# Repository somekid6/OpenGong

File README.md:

# OpenGong — Multilateration Electronic Target

> [!WARNING]
> **Work in progress.** OpenGong is incomplete and not yet fully built or tested. Designs, firmware and documentation may change, and parts of the system may not work as described. Build at your own risk.

Five piezo sensors bonded to the back of an AR500 steel plate locate bullet impacts to within about 5 mm by time-difference-of-arrival multilateration. An ESP32-S3 (Heltec WiFi LoRa 32 V3) timestamps each sensor in hardware, solves the impact position, and sends the coordinates over LoRa to a receiver at the firing line. The link is designed for 500 m, and about 1 km is a realistic planning figure on open ground. The estimated limit is 2–4 km on flat, open ground with clear line of sight. These are link-budget estimates, so run a [signal range test](docs/System-Design.md#96-signal-range-test) at your own site. It works with any single-projectile round the plate is rated for, from .22 LR to full-power rifle; shotgun pellets are not supported.

## Build guide

The [OpenGong wiki](https://github.com/somekid6/OpenGong/wiki) walks through the whole build in eleven steps. Start with [Step 1: Get the Project Files](https://github.com/somekid6/OpenGong/wiki/Step-1-Get-the-Project-Files).

1. [Get the Project Files](https://github.com/somekid6/OpenGong/wiki/Step-1-Get-the-Project-Files)
2. [Parts and Tools](https://github.com/somekid6/OpenGong/wiki/Step-2-Parts-and-Tools)
3. [Order the Analog Board](https://github.com/somekid6/OpenGong/wiki/Step-3-Order-the-Analog-Board)
4. [Print the Jig and Covers](https://github.com/somekid6/OpenGong/wiki/Step-4-Print-the-Jig-and-Covers)
5. [Assemble the Analog Board](https://github.com/somekid6/OpenGong/wiki/Step-5-Assemble-the-Analog-Board)
6. [Flash the Firmware](https://github.com/somekid6/OpenGong/wiki/Step-6-Flash-the-Firmware)
7. [Glue and Wire the Sensors](https://github.com/somekid6/OpenGong/wiki/Step-7-Glue-and-Wire-the-Sensors)
8. [Bench Bring-Up](https://github.com/somekid6/OpenGong/wiki/Step-8-Bench-Bring-Up)
9. [Calibrate](https://github.com/somekid6/OpenGong/wiki/Step-9-Calibrate)
10. [Enclosure and Mounting](https://github.com/somekid6/OpenGong/wiki/Step-10-Enclosure-and-Mounting)
11. [Range Setup and First Shots](https://github.com/somekid6/OpenGong/wiki/Step-11-Range-Setup-and-First-Shots)

If something doesn't work, see [Troubleshooting](https://github.com/somekid6/OpenGong/wiki/Troubleshooting) for symptoms and fixes covering bring-up, calibration and the radio link.

## Reference documents

The documents below hold the design reasoning, schematics and source files that the build guide draws on.

- [System design](docs/System-Design.md): architecture, accuracy budget, sensors, mounting and enclosure, solver, calibration, radio link and range, ammunition and safety, bill of materials and build plan.
- [Wiring diagram](docs/Wiring-Diagram.md): system wiring, per-channel circuit, shared bias/threshold/power, Heltec pin map and channel-to-part map.
- [Analog board PCB](hardware/analog-board/README.md): ready-to-order gerbers, BOM, assembly and bring-up for the 5-channel front end that the Heltec V3 plugs into, plus the KiCad project.
- [Placement jig](Placement%20Jig/README.md): the OpenSCAD sensor and punch-guide jig for rectangular and round plates, covering parameters, export, printing, assembly and calibration points.
- [Sensor covers](Sensor%20Cover/README.md): OpenSCAD cover pods and cable clips held on by rubber-coated pot magnets, with the magnet and hardware list, printing, fitting and removal for calibration.
- [Box brackets](Box%20Bracket/README.md): example OpenSCAD sketches of the bracket that hangs the electronics box from the plate's hanger bolts, for plates with one or two hanger holes. Square tube spacers and straight aluminium flat bar, with no bending, and a preview that checks clearance to the sensor pods. Custom fit to your plate.
- [Firmware](firmware/README.md): ESP32-S3 target (hardware capture, solver, on-board calibration, LoRa) and receiver firmware, with build, bring-up and calibration steps. The receiver hosts a [web app](firmware/README.md#web-app) over its own Wi-Fi that draws your plate to scale with the hits and an MOA/MIL grid on any phone or laptop.

The receiver's web app on a phone and a laptop: the plate to scale, numbered hits, an MOA or mil grid and the group statistics. It can also walk you through calibrating the target from your phone ([firmware README](firmware/README.md#web-app)).

<details>
<summary>Web app screenshots</summary>

</details>

## Safety

Follow your plate maker's rating for the round you shoot. [System design §10](docs/System-Design.md#10-ammunition-and-safety-read-before-shooting) lists commonly cited plate thicknesses and minimum distances per caliber. Never use steel-core or penetrator rounds. Keep all electronics and cables fully behind the plate under a steel shield.

## References and acknowledgements

OpenGong builds on the work of **Matthew Waterman and Donato Salazar**, whose Northern Illinois University senior design project showed that an accurate electronic target can be built from cheap, easy-to-find parts. Thank you both for publishing your research and source code so others could build on it.

- M. Waterman and D. Salazar, "Electronic Target," Senior Design II, Northern Illinois University (advisor: Dr. Abul Azad), December 8, 2011. [Paper (PDF)](docs/Reference%20Materials/Waterman%20Salazar%20-%20Electronic%20Targets.pdf) · [Presentation with notes (PDF)](docs/Reference%20Materials/Waterman%20Salazar%20Tech%20478%20Presentation%20With%20Notes.pdf). These were first published on etarg.net, which is no longer online, so copies are kept here.

Their paper sets out the core approach this project uses: timing the impact wave at piezo sensors on a hard target with threshold comparators, then locating the hit by time-difference-of-arrival multilateration. It also names the error sources this design sets out to remove. [System design §1](docs/System-Design.md#1-summary) compares the two.

AI assistance: [Claude](https://www.anthropic.com/claude), by Anthropic, helped with the design analysis, firmware, documentation and diagrams. This project wouldn't have been possible with my personal time constraints and skill level.

## License

You can use, modify, share and sell OpenGong, as long as you credit the original author and keep the license notice. Each part of the project has a license suited to it:

| Part | License |
|---|---|
| Hardware designs ([hardware](hardware/), [Placement Jig](Placement%20Jig/), [Sensor Cover](Sensor%20Cover/), [Box Bracket](Box%20Bracket/)) | [CERN-OHL-P v2](LICENSES/CERN-OHL-P-2.0.txt) |
| Firmware and web app ([firmware](firmware/)) | [MIT](firmware/LICENSE) |
| Documentation, images and everything else | [CC BY 4.0](LICENSES/CC-BY-4.0.txt) |

To give credit, write something like: *Based on OpenGong by somekid6 (some_kid6) – https://github.com/somekid6/OpenGong*, and say whether you changed it. See [LICENSE](LICENSE) for details.

The third-party papers in [docs/Reference Materials](docs/Reference%20Materials/) remain the work of their authors and are not covered by these licenses.

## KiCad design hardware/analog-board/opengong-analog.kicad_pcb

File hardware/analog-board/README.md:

# OpenGong analog front-end board

The one custom circuit board in OpenGong. It carries the five sensor channels from [Wiring Diagram](../../docs/Wiring-Diagram.md). The target's Heltec WiFi LoRa 32 V3 plugs straight into it on two header sockets. The receiver is a stock Heltec V3 and needs no custom board.

| | |
| --- | --- |
| Size | 100 × 100 mm, 2 layers, 1.6 mm FR-4, 1 oz copper |
| Smallest feature | 0.25 mm track, 0.2 mm clearance, 0.3 mm drill (any budget fab can make it) |
| Parts | Hand-solderable: 0805 passives, SOIC-8 ICs, SOT-23 diodes, through-hole connectors and trimmer |
| Checks | KiCad 10 DRC with 0 errors and 0 unconnected items, schematic-to-board parity clean, ERC 0 errors |

## Files

| File | What it's for |
| --- | --- |
| [`fab/opengong-analog-gerbers.zip`](fab/opengong-analog-gerbers.zip) | **Upload this to the board house.** Gerbers (copper, mask, silkscreen, paste, outline) plus Excellon drill files. |
| [`fab/opengong-analog-bom.csv`](fab/opengong-analog-bom.csv) | Bill of materials, grouped by value, with suggested part numbers. |
| [`docs/opengong-analog-schematic.pdf`](docs/opengong-analog-schematic.pdf) | Schematic. |
| [`docs/opengong-analog-assembly.pdf`](docs/opengong-analog-assembly.pdf) | Assembly drawing: part outlines and reference designators, for finding where each part goes. |
| `opengong-analog.kicad_pro / .kicad_sch / .kicad_pcb` | The KiCad 10 project, if you want to change the board. |
| [`tools/`](tools/) | Scripts that generate the schematic and board and export everything. |

## 1. Order the bare boards

1. Go to any PCB service (JLCPCB, PCBWay, OSH Park, Aisler and so on) and upload `fab/opengong-analog-gerbers.zip`. The site reads the size (100 × 100 mm) and layer count (2) from the files.
2. Keep the default options: 1.6 mm thickness, 1 oz copper, HASL or ENIG finish, any solder-mask colour. Order the minimum quantity (usually 5). Spares are handy.
3. Don't order a stencil or assembly; you'll solder the parts yourself.

At the larger budget fabs, 100 × 100 mm is the largest size in the cheapest price tier.

> **Check the Heltec row spacing before you order.** Heltec's V3 datasheet gives the module as 50.2 × 25.5 mm with two 18-pin rows at 2.54 mm pitch, but doesn't print the distance between the two rows. This board uses **22.86 mm (0.9 in) centre to centre**, which puts both rows 1.32 mm in from the module edges. Measure your module with calipers; if it differs, see [Changing the board](#6-changing-the-board).

## 2. Get the parts

[`fab/opengong-analog-bom.csv`](fab/opengong-analog-bom.csv) is the full list. In summary:

| Qty | Part | Notes |
| --- | --- | --- |
| 3 | OPA2350UA, SOIC-8 | U1–U3 |
| 3 | TLV3502AID, SOIC-8 | U4–U6. Must be a push-pull part; an LMV393 (open-drain) would need pull-ups the board doesn't have. |
| 5 | BAV99, SOT-23 | D1–D5 |
| 5 | Phoenix PT 1,5/2-3,5-H (1984617), 3.5 mm 2-way screw terminal | J1–J5, one per sensor |
| 2 | 1×18 female header, 2.54 mm, 8.5 mm tall | J7, J8 for the Heltec |
| 1 | Bourns 3296W 10 k multi-turn trimmer | RV1, threshold |
| 1 | 0805 ferrite bead, ~220 Ω at 100 MHz | FB1 |
| — | 0805 resistors, 1 % | 10k ×8, 1M ×5, 3.3k ×5, 9.1k ×5, 1k ×5, 100 Ω ×5 |
| — | 0805 capacitors | 1 nF **C0G/NP0** ×5, 100 nF ×7, 1 µF ×2, 10 µF ×1 |

The test points (TP1–TP9) are bare pads. Clip a scope probe to a short loop of resistor-lead offcut soldered into each one.

## 3. Assemble

Use a fine-tip iron, flux and 0.5 mm solder. Fit low parts first so the board sits flat while you work:

1. **ICs** (U1–U6): check that the pin-1 dot matches the silkscreen mark. Tack one corner pin, check alignment, then solder the rest. U1–U3 are OPA2350 (op-amps, lower row); U4–U6 are TLV3502 (comparators, upper row).
2. **BAV99 diodes** (D1–D5): the single pad (pin 3) faces right.
3. **0805 resistors and capacitors.** Reference designators follow the channel: for channel *n*, `Rn1` 10k, `Rn2` 1M, `Rn3` 3.3k, `Rn4` 100 Ω, `Rn5` 9.1k (Rf), `Rn6` 1k (Rg), `Cn1` 1 nF. For example, R35 is channel 3's Rf. The shared parts are R1/R2/C1 (VMID divider), R3/C2 (threshold filter), FB1/C3/C4 (analog supply) and C101–C106 (one 100 nF per IC). The spare comparator half, U6B, is tied off on the board and needs nothing fitted.
4. **Through-hole parts:** RV1, the screw terminals (wire openings toward the board edge), then the two 18-pin sockets. To keep the sockets straight, plug them onto the Heltec's pins, set the module in place, and solder the sockets with the Heltec fitted.
5. Solder the Heltec's own pin headers **pointing down, away from the OLED**, if they aren't already fitted.

## 4. Bring-up

Bring the board up in this order:

1. **Attach the LoRa antenna before powering.** Transmitting into an open U.FL connector can damage the radio.
2. With a meter, check that +3V3A (TP8) to GND (TP9) isn't a short.
3. Plug in the Heltec (OLED up, USB-C at the board edge) and power it over USB.
4. Measure TP8 ≈ 3.3 V, TP6 (VMID) ≈ 1.65 V, and TP7 (VTH). Turn RV1 until VTH sits a little above VMID: the comparators fire when an amplifier output rises past VTH, and the amplifier rests at VMID.
5. Follow the firmware [bring-up and calibration steps](../../firmware/README.md). Raise VTH until the comparators stop firing on noise, then add a little margin ([Wiring Diagram §3](../../docs/Wiring-Diagram.md#3-shared-bias-threshold-and-power)).
6. TP1–TP5 (AMP1–AMP5) are the amplifier outputs, the best place to watch each sensor with a scope.

Wiring the sensors: each terminal's **left** screw is the signal (piezo ceramic/centre electrode) and the **right** screw is GND (cable shield and brass). Tie each shield at the board end only. Use thin 2-core shielded cable, one core for the ceramic and one for the brass; see [Wiring Diagram §6](../../docs/Wiring-Diagram.md#6-wiring-notes) for the cable spec.

## 5. Design notes

- The bottom layer is an almost unbroken ground plane, with a few short crossover links. The top layer carries the signals plus a second ground pour stitched to the bottom one. Every SMD ground pad has its own via.
- Signal flows up each column, from the terminal at the bottom edge to the Heltec at the top, so the noisy digital module stays at the opposite end from the sensor inputs.
- Channel-to-part and pin map are as in [Wiring Diagram §4–5](../../docs/Wiring-Diagram.md#4-heltec-v3-connections). TRIG1–5 go to GPIO2, 4, 5, 6 and 7 on Heltec header J3 (board J8). Header J2 (board J7) only connects GND and holds the module. 3V3 comes from J3 pins 2–3 through FB1. GPIO48 is left unconnected for the firmware's capture-sync line.
- The board has four M3 mounting holes.

## 6. Changing the board

The schematic and board are generated from [`tools/design.py`](tools/design.py), which holds the parts and netlist. Run everything with KiCad 10's bundled Python:

```sh
"<KiCad 10>/bin/python.exe" -I tools/build.py            # regenerate, re-route, check, export
"<KiCad 10>/bin/python.exe" -I tools/build.py --export   # check and export only (after hand edits in KiCad)
```

`build.py` stops if DRC (with schematic parity) or ERC reports any error. For the build to finish, both checks must be clean.

- **Part values** (gain, filter): edit `design.py` and run a full build, or change the value in KiCad and run `--export`.
- **Heltec row spacing:** change `HELTEC_ROW_SPACING` in [`tools/gen_board.py`](tools/gen_board.py) and run a full build.
- **Hand edits in KiCad:** open `opengong-analog.kicad_pro`, edit, save, then run `build.py --export`. A full `build.py` run regenerates both files from the scripts and overwrites hand edits.

`gen_board.py` places the parts and routes them with a small grid router ([`tools/router.py`](tools/router.py)). KiCad's DRC is the final check on its output.

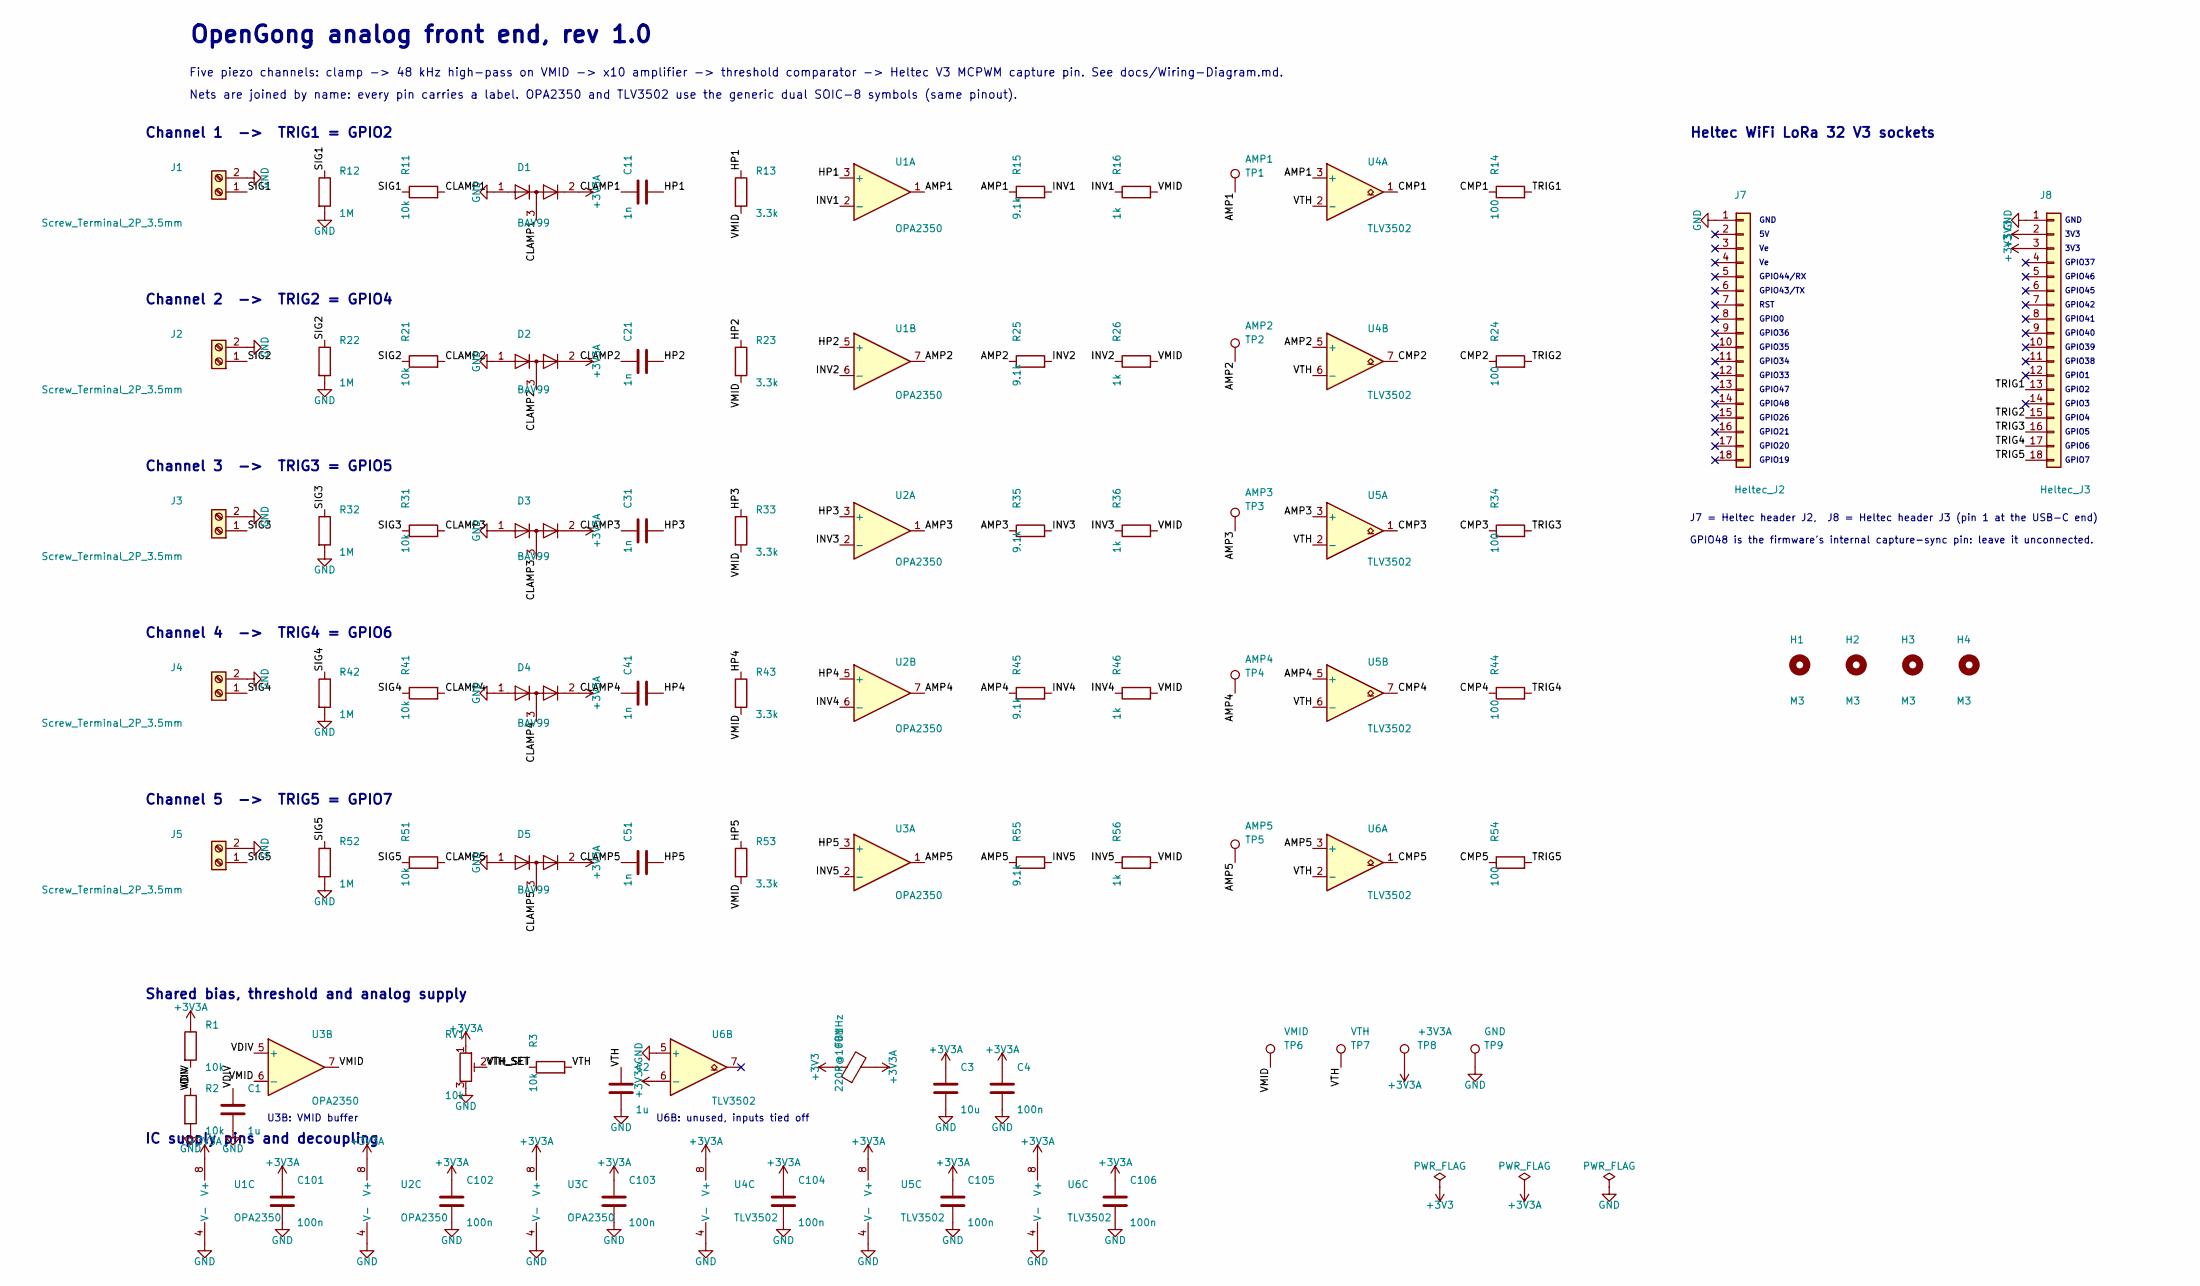
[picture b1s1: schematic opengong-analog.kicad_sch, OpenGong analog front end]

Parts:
C1, C2: 1u; C_0805_2012Metric_Pad1.18x1.45mm_HandSolder; MPN 0805 X7R, 16 V or more
C3: 10u; C_0805_2012Metric_Pad1.18x1.45mm_HandSolder; MPN 0805 X5R/X7R, 10 V or more
C4, C101, C102, C103, C104, C105, C106: 100n; C_0805_2012Metric_Pad1.18x1.45mm_HandSolder; MPN 0805 X7R, 16 V or more
C11, C21, C31, C41, C51: 1n; C_0805_2012Metric_Pad1.18x1.45mm_HandSolder; MPN 0805 C0G/NP0, 50 V
D1, D2, D3, D4, D5: BAV99; SOT-23_Handsoldering; MPN Nexperia BAV99,215 (SOT-23)
FB1: 220R@100MHz; L_0805_2012Metric_Pad1.05x1.20mm_HandSolder; MPN Murata BLM21PG221SN1D (0805, 220R@100MH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
H1, H2, H3, H4: M3; MountingHole_3.2mm_M3
J1, J2, J3, J4, J5: Screw_Terminal_2P_3.5mm; TerminalBlock_Phoenix_PT-1,5-2-3.5-H_1x02_P3.50mm_Horizontal; MPN Phoenix Contact 1984617 (PT 1,5/2-3,5-H)
J7: Heltec_J2; PinSocket_1x18_P2.54mm_Vertical; MPN 1x18 female header, 2.54 mm, 8.5 mm tal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
J8: Heltec_J3; PinSocket_1x18_P2.54mm_Vertical; MPN 1x18 female header, 2.54 mm, 8.5 mm tal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
R1, R2, R3, R11, R21, R31, R41, R51: 10k; R_0805_2012Metric_Pad1.20x1.40mm_HandSolder; MPN 0805 thick film, 1 %
R12, R22, R32, R42, R52: 1M; R_0805_2012Metric_Pad1.20x1.40mm_HandSolder; MPN 0805 thick film, 1 %
R13, R23, R33, R43, R53: 3.3k; R_0805_2012Metric_Pad1.20x1.40mm_HandSolder; MPN 0805 thick film, 1 %
R14, R24, R34, R44, R54: 100; R_0805_2012Metric_Pad1.20x1.40mm_HandSolder; MPN 0805 thick film, 1 %
R15, R25, R35, R45, R55: 9.1k; R_0805_2012Metric_Pad1.20x1.40mm_HandSolder; MPN 0805 thick film, 1 %
R16, R26, R36, R46, R56: 1k; R_0805_2012Metric_Pad1.20x1.40mm_HandSolder; MPN 0805 thick film, 1 %
RV1: 10k; Potentiometer_Bourns_3296W_Vertical; MPN Bourns 3296W-1-103LF (10k, 25-turn)
TP1: AMP1; TestPoint_THTPad_D1.5mm_Drill0.7mm
TP2: AMP2; TestPoint_THTPad_D1.5mm_Drill0.7mm
TP3: AMP3; TestPoint_THTPad_D1.5mm_Drill0.7mm
TP4: AMP4; TestPoint_THTPad_D1.5mm_Drill0.7mm
TP5: AMP5; TestPoint_THTPad_D1.5mm_Drill0.7mm
TP6: VMID; TestPoint_THTPad_D1.5mm_Drill0.7mm
TP7: VTH; TestPoint_THTPad_D1.5mm_Drill0.7mm
TP8: +3V3A; TestPoint_THTPad_D1.5mm_Drill0.7mm
TP9: GND; TestPoint_Loop_D2.50mm_Drill1.0mm
U1, U2, U3: OPA2350; SOIC-8_3.9x4.9mm_P1.27mm; MPN TI OPA2350UA (SOIC-8)
U4, U5, U6: TLV3502; SOIC-8_3.9x4.9mm_P1.27mm; MPN TI TLV3502AID (SOIC-8)

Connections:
+3V3: FB1.1, J8.2, J8.3
+3V3A: C3.1, C4.1, C101.1, C102.1, C103.1, C104.1, C105.1, C106.1, D1.2 (A), D2.2 (A), D3.2 (A), D4.2 (A), D5.2 (A), FB1.2, R1.1, RV1.1, TP8.1, U1.8 (V+), U2.8 (V+), U3.8 (V+), U4.8 (V+), U5.8 (V+), U6.6 (-), U6.8 (V+)
/AMP1: R15.1, TP1.1, U1.1, U4.3 (+)
/AMP2: R25.1, TP2.1, U1.7, U4.5 (+)
/AMP3: R35.1, TP3.1, U2.1, U5.3 (+)
/AMP4: R45.1, TP4.1, U2.7, U5.5 (+)
/AMP5: R55.1, TP5.1, U3.1, U6.3 (+)
/CLAMP1: C11.1, D1.3 (K), R11.2
/CLAMP2: C21.1, D2.3 (K), R21.2
/CLAMP3: C31.1, D3.3 (K), R31.2
/CLAMP4: C41.1, D4.3 (K), R41.2
/CLAMP5: C51.1, D5.3 (K), R51.2
/CMP1: R14.1, U4.1
/CMP2: R24.1, U4.7
/CMP3: R34.1, U5.1
/CMP4: R44.1, U5.7
/CMP5: R54.1, U6.1
/HP1: C11.2, R13.1, U1.3 (+)
/HP2: C21.2, R23.1, U1.5 (+)
/HP3: C31.2, R33.1, U2.3 (+)
/HP4: C41.2, R43.1, U2.5 (+)
/HP5: C51.2, R53.1, U3.3 (+)
/INV1: R15.2, R16.1, U1.2 (-)
/INV2: R25.2, R26.1, U1.6 (-)
/INV3: R35.2, R36.1, U2.2 (-)
/INV4: R45.2, R46.1, U2.6 (-)
/INV5: R55.2, R56.1, U3.2 (-)
/SIG1: J1.1, R11.1, R12.1
/SIG2: J2.1, R21.1, R22.1
/SIG3: J3.1, R31.1, R32.1
/SIG4: J4.1, R41.1, R42.1
/SIG5: J5.1, R51.1, R52.1
/TRIG1: J8.13, R14.2
/TRIG2: J8.15, R24.2
/TRIG3: J8.16, R34.2
/TRIG4: J8.17, R44.2
/TRIG5: J8.18, R54.2
/VDIV: C1.1, R1.2, R2.1, U3.5 (+)
/VMID: R13.2, R16.2, R23.2, R26.2, R33.2, R36.2, R43.2, R46.2, R53.2, R56.2, TP6.1, U3.6 (-), U3.7
/VTH: C2.1, R3.2, TP7.1, U4.2 (-), U4.6 (-), U5.2 (-), U5.6 (-), U6.2 (-)
/VTH_SET: R3.1, RV1.2
GND: C1.2, C2.2, C3.2, C4.2, C101.2, C102.2, C103.2, C104.2, C105.2, C106.2, D1.1 (K), D2.1 (K), D3.1 (K), D4.1 (K), D5.1 (K), J1.2, J2.2, J3.2, J4.2, J5.2, J7.1, J8.1, R2.2, R12.2, R22.2, R32.2, R42.2, R52.2, RV1.3, TP9.1, U1.4 (V-), U2.4 (V-), U3.4 (V-), U4.4 (V-), U5.4 (V-), U6.4 (V-), U6.5 (+)

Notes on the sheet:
OpenGong analog front end, rev 1.0
Five piezo channels: clamp -> 48 kHz high-pass on VMID -> x10 amplifier -> threshold comparator -> Heltec V3 MCPWM capture pin. See docs/Wiring-Diagram.md.
Nets are joined by name: every pin carries a label. OPA2350 and TLV3502 use the generic dual SOIC-8 symbols (same pinout).
Channel 1 -> TRIG1 = GPIO2
Channel 2 -> TRIG2 = GPIO4
Channel 3 -> TRIG3 = GPIO5
Channel 4 -> TRIG4 = GPIO6
Channel 5 -> TRIG5 = GPIO7
Shared bias, threshold and analog supply
U3B: VMID buffer
U6B: unused, inputs tied off
IC supply pins and decoupling
Heltec WiFi LoRa 32 V3 sockets
GND
GPIO44/RX
GPIO43/TX
RST
GPIO0
GPIO36
GPIO35
GPIO34
GPIO33
GPIO47
GPIO48
GPIO26
GPIO21
GPIO20
GPIO19
3V3
GPIO37
GPIO46
GPIO45
GPIO42
GPIO41
GPIO40
GPIO39
GPIO38
GPIO1
GPIO2
GPIO3

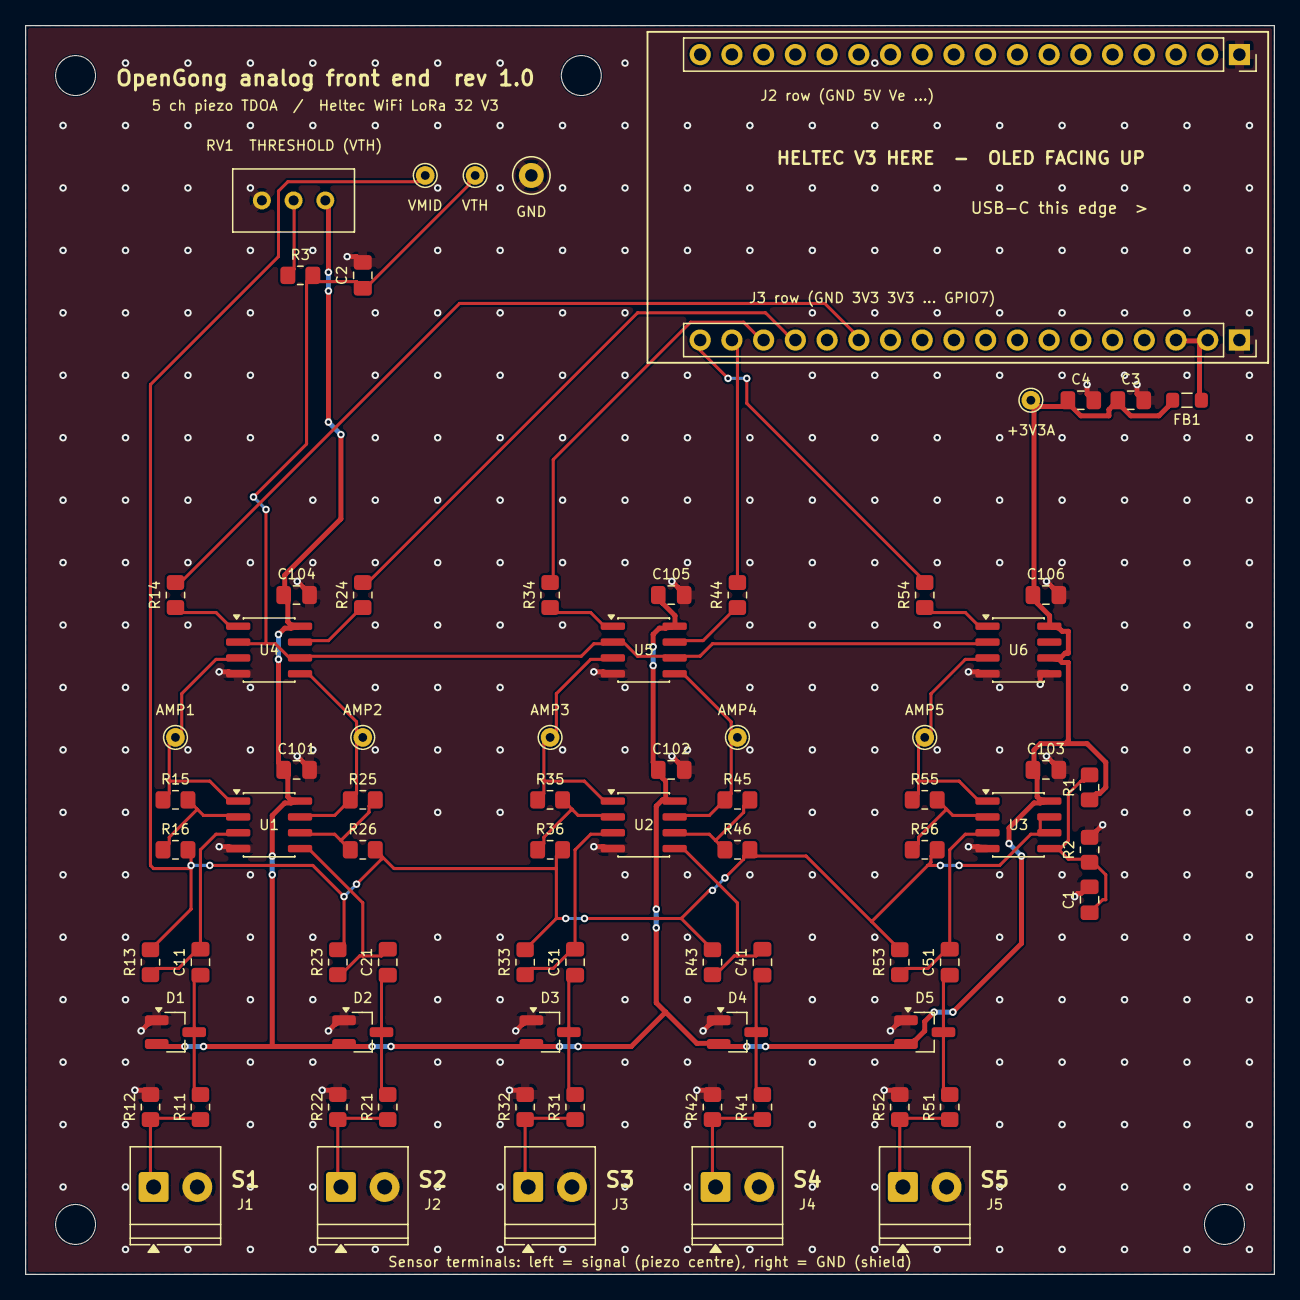
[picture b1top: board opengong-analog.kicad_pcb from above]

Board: 2 copper layers, 100.0 x 100.0 mm, 81 parts (0 on the bottom side), 42 nets.

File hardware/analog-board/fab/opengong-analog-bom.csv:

"Refs","Value","Footprint","Qty","Suggested part"
"C11,C21,C31,C41,C51","1n","Capacitor_SMD:C_0805_2012Metric_Pad1.18x1.45mm_HandSolder","5","0805 C0G/NP0, 50 V"
"C4,C101-C106","100n","Capacitor_SMD:C_0805_2012Metric_Pad1.18x1.45mm_HandSolder","7","0805 X7R, 16 V or more"
"C1,C2","1u","Capacitor_SMD:C_0805_2012Metric_Pad1.18x1.45mm_HandSolder","2","0805 X7R, 16 V or more"
"C3","10u","Capacitor_SMD:C_0805_2012Metric_Pad1.18x1.45mm_HandSolder","1","0805 X5R/X7R, 10 V or more"
"R14,R24,R34,R44,R54","100","Resistor_SMD:R_0805_2012Metric_Pad1.20x1.40mm_HandSolder","5","0805 thick film, 1 %"
"R16,R26,R36,R46,R56","1k","Resistor_SMD:R_0805_2012Metric_Pad1.20x1.40mm_HandSolder","5","0805 thick film, 1 %"
"R13,R23,R33,R43,R53","3.3k","Resistor_SMD:R_0805_2012Metric_Pad1.20x1.40mm_HandSolder","5","0805 thick film, 1 %"
"R15,R25,R35,R45,R55","9.1k","Resistor_SMD:R_0805_2012Metric_Pad1.20x1.40mm_HandSolder","5","0805 thick film, 1 %"
"R1-R3,R11,R21,R31,R41,R51","10k","Resistor_SMD:R_0805_2012Metric_Pad1.20x1.40mm_HandSolder","8","0805 thick film, 1 %"
"RV1","10k","Potentiometer_THT:Potentiometer_Bourns_3296W_Vertical","1","Bourns 3296W-1-103LF (10k, 25-turn)"
"R12,R22,R32,R42,R52","1M","Resistor_SMD:R_0805_2012Metric_Pad1.20x1.40mm_HandSolder","5","0805 thick film, 1 %"
"FB1","220R@100MHz","Inductor_SMD:L_0805_2012Metric_Pad1.05x1.20mm_HandSolder","1","Murata BLM21PG221SN1D (0805, 220R@100MHz)"
"D1-D5","BAV99","Package_TO_SOT_SMD:SOT-23_Handsoldering","5","Nexperia BAV99,215 (SOT-23)"
"J7","Heltec_J2","Connector_PinSocket_2.54mm:PinSocket_1x18_P2.54mm_Vertical","1","1x18 female header, 2.54 mm, 8.5 mm tall (e.g. Sullins PPTC181LFBN-RC)"
"J8","Heltec_J3","Connector_PinSocket_2.54mm:PinSocket_1x18_P2.54mm_Vertical","1","1x18 female header, 2.54 mm, 8.5 mm tall (e.g. Sullins PPTC181LFBN-RC)"
"U1-U3","OPA2350","Package_SO:SOIC-8_3.9x4.9mm_P1.27mm","3","TI OPA2350UA (SOIC-8)"
"J1-J5","Screw_Terminal_2P_3.5mm","TerminalBlock_Phoenix:TerminalBlock_Phoenix_PT-1,5-2-3.5-H_1x02_P3.50mm_Horizontal","5","Phoenix Contact 1984617 (PT 1,5/2-3,5-H)"
"U4-U6","TLV3502","Package_SO:SOIC-8_3.9x4.9mm_P1.27mm","3","TI TLV3502AID (SOIC-8)"

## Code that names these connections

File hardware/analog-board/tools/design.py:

"""OpenGong analog front-end board: parts and netlist (single source of truth).

Both gen_schematic.py and gen_board.py read this file. The circuit is the one in
docs/Wiring-Diagram.md; reference designators follow the board numbering
scheme described in hardware/analog-board/README.md:

  Channel n (1-5):  Jn sensor terminal, Dn clamp diode,
                    Rn1 series 10k, Rn2 bias 1M, Rn3 high-pass 3.3k,
                    Rn4 output 100R, Rn5 Rf 9.1k, Rn6 Rg 1k, Cn1 high-pass 1n,
                    TPn amplifier-output test point.
  Shared:           R1/R2 VMID divider, C1 VMID filter, RV1 + R3 + C2 threshold,
                    FB1 + C3 + C4 analog supply, C101-C106 decoupling for U1-U6,
                    TP6-TP9 VMID / VTH / +3V3A / GND test points.
"""

FP = {
    "R": "Resistor_SMD:R_0805_2012Metric_Pad1.20x1.40mm_HandSolder",
    "C": "Capacitor_SMD:C_0805_2012Metric_Pad1.18x1.45mm_HandSolder",
    "FB": "Inductor_SMD:L_0805_2012Metric_Pad1.05x1.20mm_HandSolder",
    "SOIC8": "Package_SO:SOIC-8_3.9x4.9mm_P1.27mm",
    "SOT23": "Package_TO_SOT_SMD:SOT-23_Handsoldering",
    "TRIM": "Potentiometer_THT:Potentiometer_Bourns_3296W_Vertical",
    "TERM": "TerminalBlock_Phoenix:TerminalBlock_Phoenix_PT-1,5-2-3.5-H_1x02_P3.50mm_Horizontal",
    "SOCK18": "Connector_PinSocket_2.54mm:PinSocket_1x18_P2.54mm_Vertical",
    "TP": "TestPoint:TestPoint_THTPad_D1.5mm_Drill0.7mm",
    "TPLOOP": "TestPoint:TestPoint_Loop_D2.50mm_Drill1.0mm",
    "HOLE": "MountingHole:MountingHole_3.2mm_M3",
}

SYM = {
    "R": "Device:R",
    "C": "Device:C",
    "FB": "Device:FerriteBead",
    "OPAMP": "Amplifier_Operational:LM2904",   # generic dual op-amp, OPA2350 pinout
    "CMP": "Comparator:LM2903",                # generic dual comparator, TLV3502 pinout
    "BAV99": "Diode:BAV99",
    "TRIM": "Device:R_Potentiometer_Trim",
    "TERM": "Connector:Screw_Terminal_01x02",
    "CONN18": "Connector_Generic:Conn_01x18",
    "TP": "Connector:TestPoint",
    "HOLE": "Mechanical:MountingHole",
}

# Suggested manufacturer part numbers (any equivalent works).
MPN = {
    "OPA2350": "TI OPA2350UA (SOIC-8)",
    "TLV3502": "TI TLV3502AID (SOIC-8)",
    "BAV99": "Nexperia BAV99,215 (SOT-23)",
    "FB": "Murata BLM21PG221SN1D (0805, 220R@100MHz)",
    "TRIM": "Bourns 3296W-1-103LF (10k, 25-turn)",
    "TERM": "Phoenix Contact 1984617 (PT 1,5/2-3,5-H)",
    "SOCK18": "1x18 female header, 2.54 mm, 8.5 mm tall (e.g. Sullins PPTC181LFBN-RC)",
}

PARTS = []      # dicts: ref, kind, value, fp, sym, pins{pad: net}, note
NC = None       # marker for an unconnected pin


def part(ref, kind, value, pins, fp=None, sym=None, note=""):
    PARTS.append(dict(ref=ref, kind=kind, value=value, pins=pins,
                      fp=FP[fp or kind], sym=SYM[sym or kind], note=note))


# Channel -> (op-amp ref, half) and (comparator ref, half), per Wiring-Diagram.md section 5.
CHANNELS = range(1, 6)
AMP = {1: ("U1", "A"), 2: ("U1", "B"), 3: ("U2", "A"), 4: ("U2", "B"), 5: ("U3", "A")}
CMP = {1: ("U4", "A"), 2: ("U4", "B"), 3: ("U5", "A"), 4: ("U5", "B"), 5: ("U6", "A")}
HALF = {"A": {"out": "1", "inv": "2", "non": "3"}, "B": {"out": "7", "inv": "6", "non": "5"}}

# Heltec header pin carrying each channel's trigger (Heltec J3 = board J8, Heltec J2 = board J7).
TRIG_PIN = {1: ("J8", "13"), 2: ("J8", "15"), 3: ("J8", "16"), 4: ("J8", "17"), 5: ("J8", "18")}
GPIO = {1: 2, 2: 4, 3: 5, 4: 6, 5: 7}

ICS = ("U1", "U2", "U3", "U4", "U5", "U6")
ic_pins = {u: {"4": "GND", "8": "+3V3A"} for u in ICS}

for n in CHANNELS:
    sig, clamp, hp, fb, amp, cmp_, trig = (f"SIG{n}", f"CLAMP{n}", f"HP{n}", f"INV{n}",
                                           f"AMP{n}", f"CMP{n}", f"TRIG{n}")
    part(f"J{n}", "TERM", "Screw_Terminal_2P_3.5mm", {"1": sig, "2": "GND"},
         note=f"Piezo PZ{n}: pin 1 = ceramic/centre (signal), pin 2 = shield/brass (GND)")
    part(f"R{n}2", "R", "1M", {"1": sig, "2": "GND"})
    part(f"R{n}1", "R", "10k", {"1": sig, "2": clamp})
    part(f"D{n}", "BAV99", "BAV99", {"1": "GND", "2": "+3V3A", "3": clamp}, fp="SOT23",
         note="Pad 1 anode D1 = GND, pad 2 cathode D2 = +3V3A, pad 3 common")
    part(f"C{n}1", "C", "1n", {"1": clamp, "2": hp}, note="C0G/NP0")
    part(f"R{n}3", "R", "3.3k", {"1": hp, "2": "VMID"})
    part(f"R{n}5", "R", "9.1k", {"1": amp, "2": fb}, note="Rf; 4.7k for gain 5.7")
    part(f"R{n}6", "R", "1k", {"1": fb, "2": "VMID"}, note="Rg")
    part(f"R{n}4", "R", "100", {"1": cmp_, "2": trig})
    part(f"TP{n}", "TP", f"AMP{n}", {"1": amp})
    u, h = AMP[n]
    ic_pins[u].update({HALF[h]["non"]: hp, HALF[h]["inv"]: fb, HALF[h]["out"]: amp})
    u, h = CMP[n]
    ic_pins[u].update({HALF[h]["non"]: amp, HALF[h]["inv"]: "VTH", HALF[h]["out"]: cmp_})

# U3B: VMID buffer (voltage follower on the divider).
# U6B: unused comparator half, inputs tied off (+ to GND, - to +3V3A) so its output stays low.
ic_pins["U3"].update({"5": "VDIV", "6": "VMID", "7": "VMID"})
ic_pins["U6"].update({"5": "GND", "6": "+3V3A", "7": NC})

for u in ("U1", "U2", "U3"):
    part(u, "SOIC8", "OPA2350", ic_pins[u], sym="OPAMP",
         note={"U3": "A = channel 5, B = VMID buffer"}.get(u, ""))
for u in ("U4", "U5", "U6"):
    part(u, "SOIC8", "TLV3502", ic_pins[u], sym="CMP",
         note={"U6": "A = channel 5, B unused (inputs tied off)"}.get(u, ""))

for i, u in enumerate(ICS):
    part(f"C10{i + 1}", "C", "100n", {"1": "+3V3A", "2": "GND"}, note=f"Decouples {u}")

# Shared bias, threshold and supply (Wiring-Diagram.md section 3).
part("R1", "R", "10k", {"1": "+3V3A", "2": "VDIV"}, note="VMID divider top")
part("R2", "R", "10k", {"1": "VDIV", "2": "GND"}, note="VMID divider bottom")
part("C1", "C", "1u", {"1": "VDIV", "2": "GND"}, note="VMID filter")
part("RV1", "TRIM", "10k", {"1": "+3V3A", "2": "VTH_SET", "3": "GND"}, note="Threshold adjust")
part("R3", "R", "10k", {"1": "VTH_SET", "2": "VTH"})
part("C2", "C", "1u", {"1": "VTH", "2": "GND"}, note="VTH filter")
part("FB1", "FB", "220R@100MHz", {"1": "+3V3", "2": "+3V3A"})
part("C3", "C", "10u", {"1": "+3V3A", "2": "GND"}, note="X5R/X7R, 10 V or more")
part("C4", "C", "100n", {"1": "+3V3A", "2": "GND"})

part("TP6", "TP", "VMID", {"1": "VMID"})
part("TP7", "TP", "VTH", {"1": "VTH"})
part("TP8", "TP", "+3V3A", {"1": "+3V3A"})
part("TP9", "TP", "GND", {"1": "GND"}, fp="TPLOOP")

# Heltec WiFi LoRa 32 V3 sockets. J7 = Heltec header J2, J8 = Heltec header J3.
j7 = {str(i): NC for i in range(1, 19)}
j7.update({"1": "GND"})
j8 = {str(i): NC for i in range(1, 19)}
j8.update({"1": "GND", "2": "+3V3", "3": "+3V3", "13": "TRIG1", "15": "TRIG2", "16": "TRIG3",
           "17": "TRIG4", "18": "TRIG5"})
part("J7", "SOCK18", "Heltec_J2", j7, sym="CONN18", note="Heltec V3 header J2 (GND only; holds the module)")
part("J8", "SOCK18", "Heltec_J3", j8, sym="CONN18", note="Heltec V3 header J3 (3V3, GPIO2-7...)")

HELTEC_J2 = ["GND", "5V", "Ve", "Ve", "GPIO44/RX", "GPIO43/TX", "RST", "GPIO0", "GPIO36",
             "GPIO35", "GPIO34", "GPIO33", "GPIO47", "GPIO48", "GPIO26", "GPIO21", "GPIO20", "GPIO19"]
HELTEC_J3 = ["GND", "3V3", "3V3", "GPIO37", "GPIO46", "GPIO45", "GPIO42", "GPIO41", "GPIO40",
             "GPIO39", "GPIO38", "GPIO1", "GPIO2", "GPIO3", "GPIO4", "GPIO5", "GPIO6", "GPIO7"]

for i in range(1, 5):
    part(f"H{i}", "HOLE", "M3", {}, note="Mounting hole")

POWER_NETS = {"GND", "+3V3", "+3V3A"}

# Per-part BOM fields shared by the schematic, board and BOM.
for _p in PARTS:
    _p["mpn"] = MPN.get(_p["value"]) or MPN.get(_p["kind"]) or MPN.get(
        {"BAV99": "BAV99"}.get(_p["value"], ""), "")
    _p["in_bom"] = _p["kind"] not in ("HOLE", "TP", "TPLOOP")
    if not _p["mpn"] and _p["kind"] == "R":
        _p["mpn"] = "0805 thick film, 1 %"
    if not _p["mpn"] and _p["kind"] == "C":
        _p["mpn"] = {"1n": "0805 C0G/NP0, 50 V", "10u": "0805 X5R/X7R, 10 V or more"}.get(
            _p["value"], "0805 X7R, 16 V or more")


def board_net(name):
    """Net name as KiCad derives it: power symbols are global, labels are sheet-local."""
    return name if name in POWER_NETS else "/" + name


def nets():
    out = {}
    for p in PARTS:
        for pad, net in p["pins"].items():
            if net:
                out.setdefault(net, []).append((p["ref"], pad))
    return out


if __name__ == "__main__":
    for net, pins in sorted(nets().items()):
        print(f"{net:10s} {len(pins):3d}  {' '.join(r + '.' + p for r, p in pins)}")
    print(len(PARTS), "parts")
